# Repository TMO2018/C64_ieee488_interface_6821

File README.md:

# C64_ieee488_interface_6821

ieee488-Interface for the C64 using the expansions-port with PIA 6821 published in the 64er 07/1985

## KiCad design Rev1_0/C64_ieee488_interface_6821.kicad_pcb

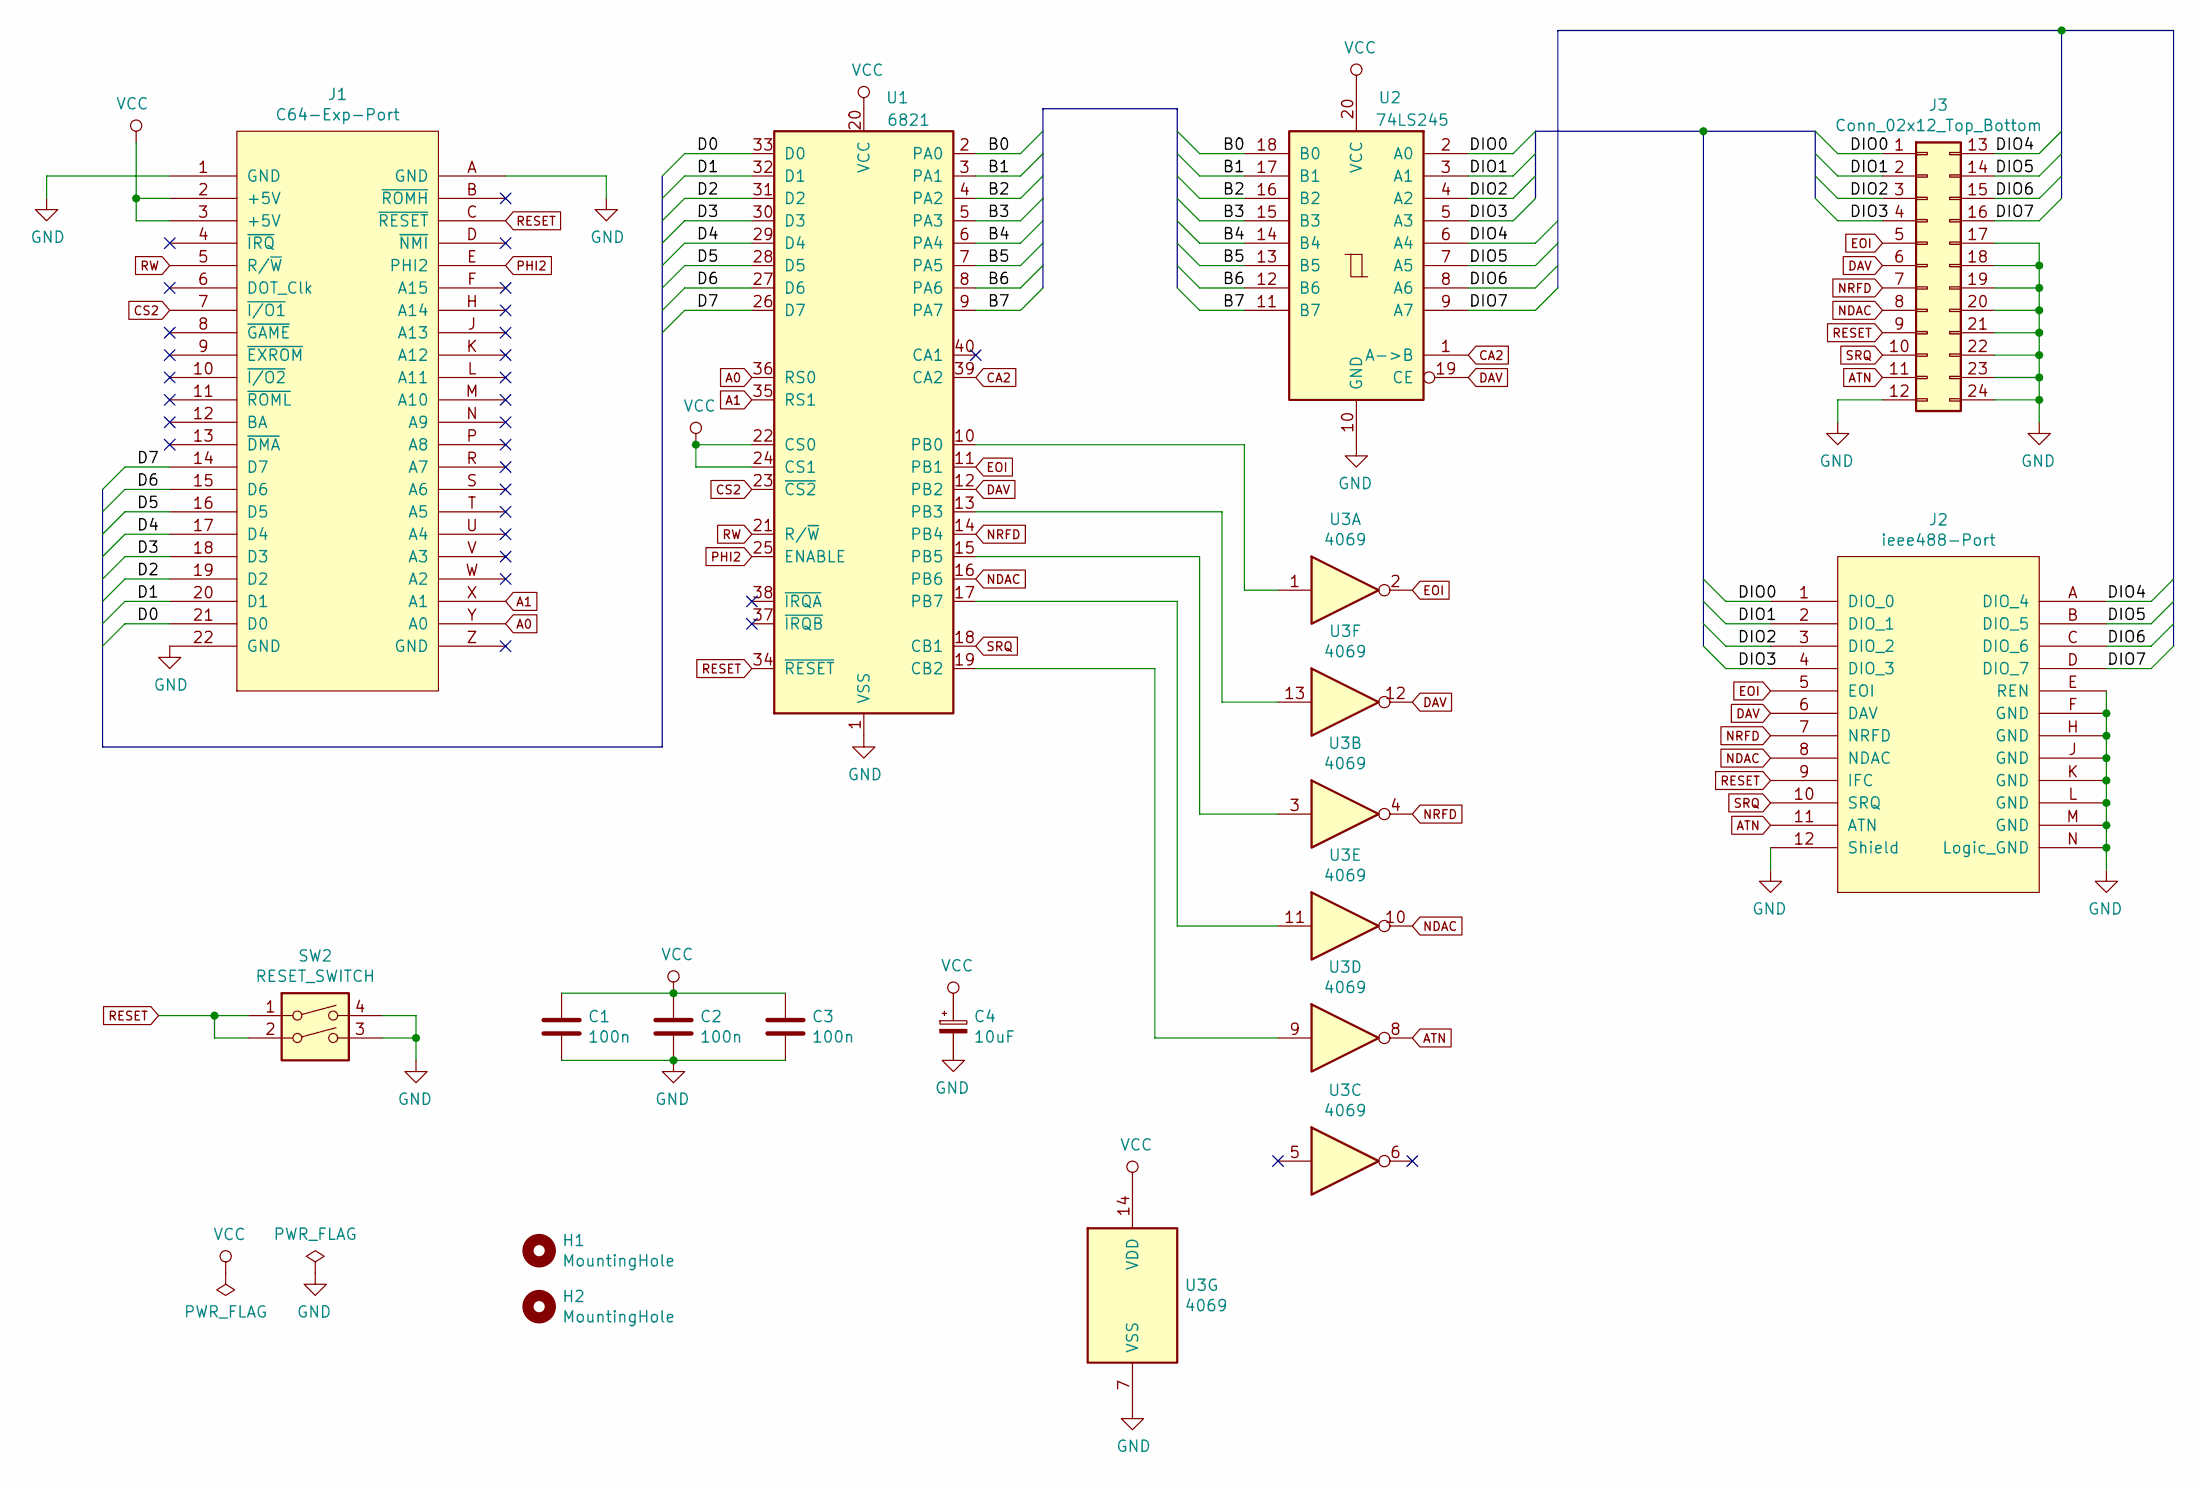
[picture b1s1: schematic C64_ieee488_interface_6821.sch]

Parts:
C1, C2, C3: 100n; C_1206_HandSoldering
C4: 10uF; CP_Radial_D5.0mm_P2.50mm
H1, H2: MountingHole; MountingHole_3.2mm_M3
J1: C64-Exp-Port; C64-Cart
J2: ieee488-Port
J3: Conn_02x12_Top_Bottom; Pin_Header_Straight_2x12_Pitch2.54mm_ieee488
SW2: RESET_SWITCH; PCB_PUSH
U1: 6821; DIP-40_W15.24mm_Socket_LongPads
U2: 74LS245; DIP-20_W7.62mm_Socket_LongPads
U3: 4069; DIP-14_W7.62mm_Socket_LongPads

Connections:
/B0: U1.2 (PA0), U2.18 (B0)
/B1: U1.3 (PA1), U2.17 (B1)
/B2: U1.4 (PA2), U2.16 (B2)
/B3: U1.5 (PA3), U2.15 (B3)
/B4: U1.6 (PA4), U2.14 (B4)
/B5: U1.7 (PA5), U2.13 (B5)
/B6: U1.8 (PA6), U2.12 (B6)
/B7: U1.9 (PA7), U2.11 (B7)
/D0: J1.21 (D0), U1.33 (D0)
/D1: J1.20 (D1), U1.32 (D1)
/D2: J1.19 (D2), U1.31 (D2)
/D3: J1.18 (D3), U1.30 (D3)
/D4: J1.17 (D4), U1.29 (D4)
/D5: J1.16 (D5), U1.28 (D5)
/D6: J1.15 (D6), U1.27 (D6)
/D7: J1.14 (D7), U1.26 (D7)
/DIO0: J2.1 (DIO_0), J3.1, U2.2 (A0)
/DIO1: J2.2 (DIO_1), J3.2, U2.3 (A1)
/DIO2: J2.3 (DIO_2), J3.3, U2.4 (A2)
/DIO3: J2.4 (DIO_3), J3.4, U2.5 (A3)
/DIO4: J2.A (DIO_4), J3.13, U2.6 (A4)
/DIO5: J2.B (DIO_5), J3.14, U2.7 (A5)
/DIO6: J2.C (DIO_6), J3.15, U2.8 (A6)
/DIO7: J2.D (DIO_7), J3.16, U2.9 (A7)
A0: J1.Y (A0), U1.36 (RS0)
A1: J1.X (A1), U1.35 (RS1)
ATN: J2.11 (ATN), J3.11, U3.8
CA2: U1.39 (CA2), U2.1 (A->B)
CS2: J1.7 (~I/O1), U1.23 (~CS2)
DAV: J2.6 (DAV), J3.6, U1.12 (PB2), U2.19 (CE), U3.12
EOI: J2.5 (EOI), J3.5, U1.11 (PB1), U3.2
GND: C1.2, C2.2, C3.2, C4.2, J1.1 (GND), J1.22 (GND), J1.A (GND), J2.12 (Shield), J2.E (REN), J2.F (GND), J2.H (GND), J2.J (GND), J2.K (GND), J2.L (GND), J2.M (GND), J2.N (Logic_GND), J3.12, J3.17, J3.18, J3.19, J3.20, J3.21, J3.22, J3.23, J3.24, SW2.3, SW2.4, U1.1 (VSS), U2.10 (GND), U3.7 (VSS)
NDAC: J2.8 (NDAC), J3.8, U1.16 (PB6), U3.10
NRFD: J2.7 (NRFD), J3.7, U1.14 (PB4), U3.4
unnamed: U1.10 (PB0), U3.1
unnamed: U1.13 (PB3), U3.13
unnamed: U1.15 (PB5), U3.3
unnamed: U1.17 (PB7), U3.11
unnamed: U1.19 (CB2), U3.9
PHI2: J1.E (PHI2), U1.25 (ENABLE)
RESET: J1.C (~RESET), J2.9 (IFC), J3.9, SW2.1, SW2.2, U1.34 (~RESET)
RW: J1.5 (R/~W), U1.21 (R/~W)
SRQ: J2.10 (SRQ), J3.10, U1.18 (CB1)
VCC: C1.1, C2.1, C3.1, C4.1, J1.2 (+5V), J1.3 (+5V), U1.20 (VCC), U1.22 (CS0), U1.24 (CS1), U2.20 (VCC), U3.14 (VDD)

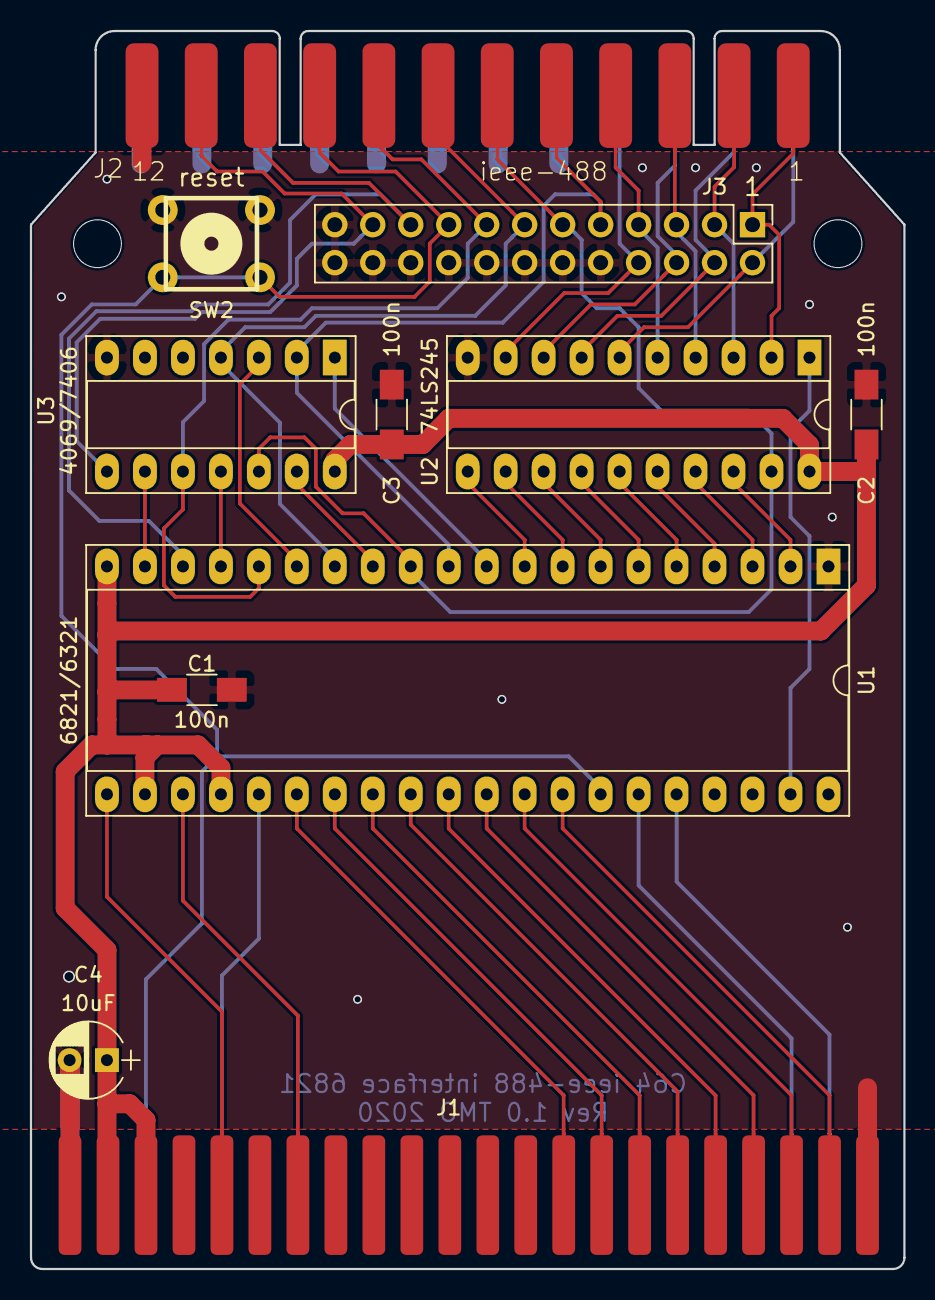
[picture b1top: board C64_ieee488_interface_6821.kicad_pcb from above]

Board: 2 copper layers, 58.4 x 82.8 mm, 13 parts (0 on the bottom side), 44 nets.

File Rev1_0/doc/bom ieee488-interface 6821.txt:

U1 : 6821 or 6321 (DIL40 15.24mm)
U2 : SN74LS245 (DIL20 7.62mm)
U3 : 4069 or SN7406 (DIL14 7.62mm)
C1,C2,C3 : capacitor ceramic 100nF SMD 1206
C4 : capacitor electrolyt radial 10uF 16V D5.0 RM2.5
SW2 : push button print 6mm
J3 : pin header 2x12 straight RM2.54
